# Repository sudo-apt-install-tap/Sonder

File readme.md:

<div align="center">

<h1>
  <b>
    SONDER
  </b> 
</h1>

<h3> <b> An ESP32 SD Card MP3 Player with a PCM5102 DAC, a 0.96" OLED and a Rotary Encoder! </b> </h3>

</div>

## **Overview**

An MP3 player built around an **ESP32** dev board and a **PCM5102** I2S DAC. It plays music from an SD card, shows the current track on a 0.96" OLED, and has 4 buttons (previous, play/pause, next, menu) plus a rotary encoder with a push switch. It lives in a 3D printed case with openings for the aux jack and USB-B port.

### Why?

It started as "wouldn't it be funny if I built my own music player" and then I spent my time fighting KiCad. Further I really wanted to make a project that deals with embedded audio decoding in C/ARDUINO IDE.

### How?
Use the firmware in [FIRMWARE](Firmware). I used ARDUINO IDE with some basic libraries like SPI, SD, vector, Audio & U8g2lib

## CAD
CAD files are available at [CAD](https://cad.onshape.com/documents/66bd644b255fcec0873fcebe/w/d2b2d33a9ff288106fcfa12e/e/8a27dd1411d3c83e2866f539?renderMode=0&uiState=6ae774908fb952af58be5994)

The case is a two part design: a main body that holds the PCB, and a separate front plate with cutouts for the OLED, the buttons and the encoder. The plate outline was drawn in KiCad on the Edge.Cuts layer and exported as a DXF. The PCB mounts to the case with heat set inserts and M2 screws, and the whole thing is 3D printed.

## Images
<div align="center">

<br> Full render<br>

---

<br> Case body

---

<br> Front plate

---

<br> PCB

---

<br> Sch

---

<br> 3D Viewer

---

</div>

## BOM

| Part | What it's for | Qty | Unit | Total | Vendor |
| --- | --- | --- | --- | --- | --- |
| [PCB](https://jlcpcb.com/) | Printed circuit board | 1 | $1.50 | $1.50 | [JLCPCB](https://jlcpcb.com/) |
| [PCM5102 I2S Digital Audio DAC Decoder Module](https://hubtronics.in/pcm5102-i2s-digital-audio-dac-decoder-module) | I2S audio output | 1 | $5.00 | $5.00 | [Hubtronics](https://hubtronics.in/pcm5102-i2s-digital-audio-dac-decoder-module) |
| [Robocraze ESP32 38 Pin](https://www.amazon.in/dp/B078MNG9D5) | MCU | 1 | $6.50 | $6.50 | [Amazon](https://www.amazon.in/dp/B078MNG9D5) |
| [SD Card Reader Module](https://robu.in/product/micro-sd-card-module/) | Reads the SD card over SPI | 1 | $1.00 | $1.00 | [Robu.in](https://robu.in/product/micro-sd-card-module/) |
| [0.96 Inch I2C/IIC 4pin OLED Display](https://robu.in/product/4pin-oled-display-module-blue-color/) | Shows the current track and volume | 1 | $2.00 | $2.00 | [Robu.in](https://robu.in/product/4pin-oled-display-module-blue-color/) |
| [Rotary Encoder with Switch](https://robu.in/product/hongyan-ec11h-7ce20p1zd20-rotary-encoder-with-push-button-switch-vertical-plug-in-5-pin/) | Volume and push | 1 | $1.00 | $1.00 | [Robu.in](https://robu.in/product/hongyan-ec11h-7ce20p1zd20-rotary-encoder-with-push-button-switch-vertical-plug-in-5-pin/) |
| [Tactile push buttons 6x6x8 [Pack of 20]](https://robu.in/product/6x6x8mm-tactile-push-button-switch-pack-of-20/) | Previous, play/pause, next, menu | 1 | $0.50 | $0.50 | [Robu.in](https://robu.in/product/6x6x8mm-tactile-push-button-switch-pack-of-20/) |
| [HIKVISION Extreme 16GB microSDXC Memory Card](https://www.amazon.in/HIKVISION-microSDXC-Compitable-Smartphones-Protection/dp/B0GVJZ56K5) | Stores the music | 1 | $6.50 | $6.50 | [Amazon](https://www.amazon.in/HIKVISION-microSDXC-Compitable-Smartphones-Protection/dp/B0GVJZ56K5) |
| [Case 3D printing](https://hackclub.slack.com/archives/C083P4FJM46/p1793539514844309) | Case | 1 | $3.00 | $3.00 | [Print Legion](https://hackclub.slack.com/archives/C083P4FJM46/p1793539514844309) |
| **Parts subtotal** | — | — | — | **$27.00** | — |
| **Tax & shipping** | — | — | — | **$3.00** | — |
| **Total** | — | — | — | **$30.00** | — |

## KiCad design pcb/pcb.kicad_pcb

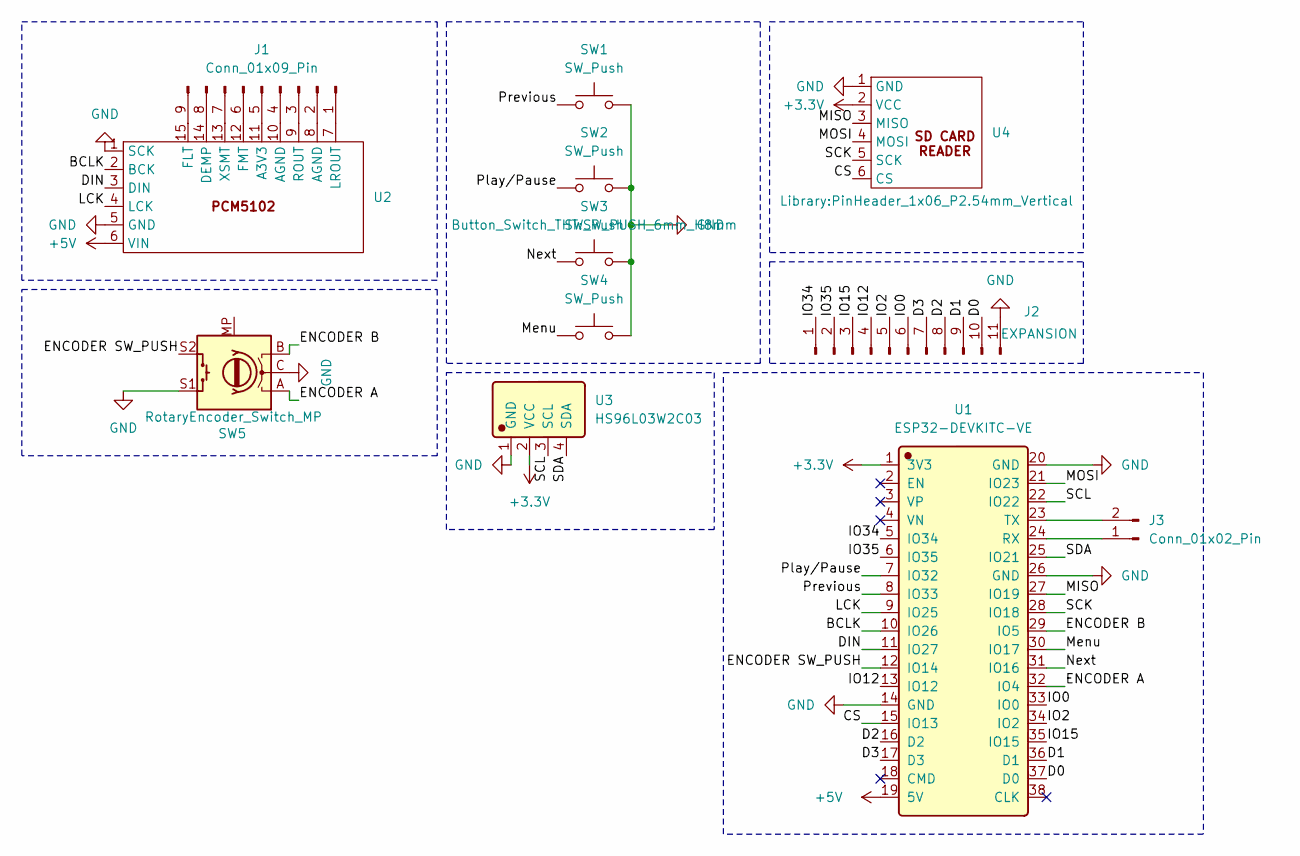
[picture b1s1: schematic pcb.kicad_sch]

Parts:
J1: Conn_01x09_Pin; PinHeader_1x09_P2.54mm_Vertical
J2: EXPANSION; PinHeader_1x11_P2.54mm_Vertical
J3: Conn_01x02_Pin; PinHeader_1x02_P2.54mm_Vertical
SW1, SW2, SW3, SW4: SW_Push; SW_PUSH_6mm_H8mm
SW5: RotaryEncoder_Switch_MP; RotaryEncoder_Alps_EC11E-Switch_Vertical_H20mm_CircularMoun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
U1: ESP32-DEVKITC-VE; Manufacturer Part ESP32-DEVKITC-VE; LCSC C20437001
U2: GY-PCM5102
U3: HS96L03W2C03; Manufacturer Part HS96L03W2C03; LCSC C5248080
U4: PinHeader_1x06_P2.54mm_Vertical

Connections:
+3.3V: U1.1 (3V3), U3.2 (VCC), U4.2 (VCC)
+5V: U1.19 (5V), U2.6 (VIN)
/BCLK: U1.10 (IO26), U2.2 (BCK)
/CS: U1.15 (IO13), U4.6 (CS)
/D0: J2.10, U1.37 (D0)
/D1: J2.9, U1.36 (D1)
/D2: J2.8, U1.16 (D2)
/D3: J2.7, U1.17 (D3)
/DIN: U1.11 (IO27), U2.3 (DIN)
/ENCODER A: SW5.A, U1.32 (IO4)
/ENCODER B: SW5.B, U1.29 (IO5)
/ENCODER SW_PUSH: SW5.S2, U1.12 (IO14)
/IO0: J2.6, U1.33 (IO0)
/IO2: J2.5, U1.34 (IO2)
/IO12: J2.4, U1.13 (IO12)
/IO15: J2.3, U1.35 (IO15)
/IO34: J2.1, U1.5 (IO34)
/IO35: J2.2, U1.6 (IO35)
/LCK: U1.9 (IO25), U2.4 (LCK)
/MISO: U1.27 (IO19), U4.3 (MISO)
/MOSI: U1.21 (IO23), U4.4 (MOSI)
/Menu: SW4.1, U1.30 (IO17)
/Next: SW3.1, U1.31 (IO16)
/Play/Pause: SW2.1, U1.7 (IO32)
/Previous: SW1.1, U1.8 (IO33)
/SCK: U1.28 (IO18), U4.5 (SCK)
/SCL: U1.22 (IO22), U3.3 (SCL)
/SDA: U1.25 (IO21), U3.4 (SDA)
GND: J2.11, SW1.2, SW2.2, SW3.2, SW4.2, SW5.C, SW5.S1, U1.14 (GND), U1.20 (GND), U1.26 (GND), U2.1 (SCK), U2.5 (GND), U3.1 (GND), U4.1 (GND)
unnamed: J1.1, U2.7 (LROUT)
unnamed: J1.2, U2.8 (AGND)
unnamed: J1.3, U2.9 (ROUT)
unnamed: J1.4, U2.10 (AGND)
unnamed: J1.5, U2.11 (A3V3)
unnamed: J1.6, U2.12 (FMT)
unnamed: J1.7, U2.13 (XSMT)
unnamed: J1.8, U2.14 (DEMP)
unnamed: J1.9, U2.15 (FLT)
unnamed: J3.1, U1.24 (RX)
unnamed: J3.2, U1.23 (TX)

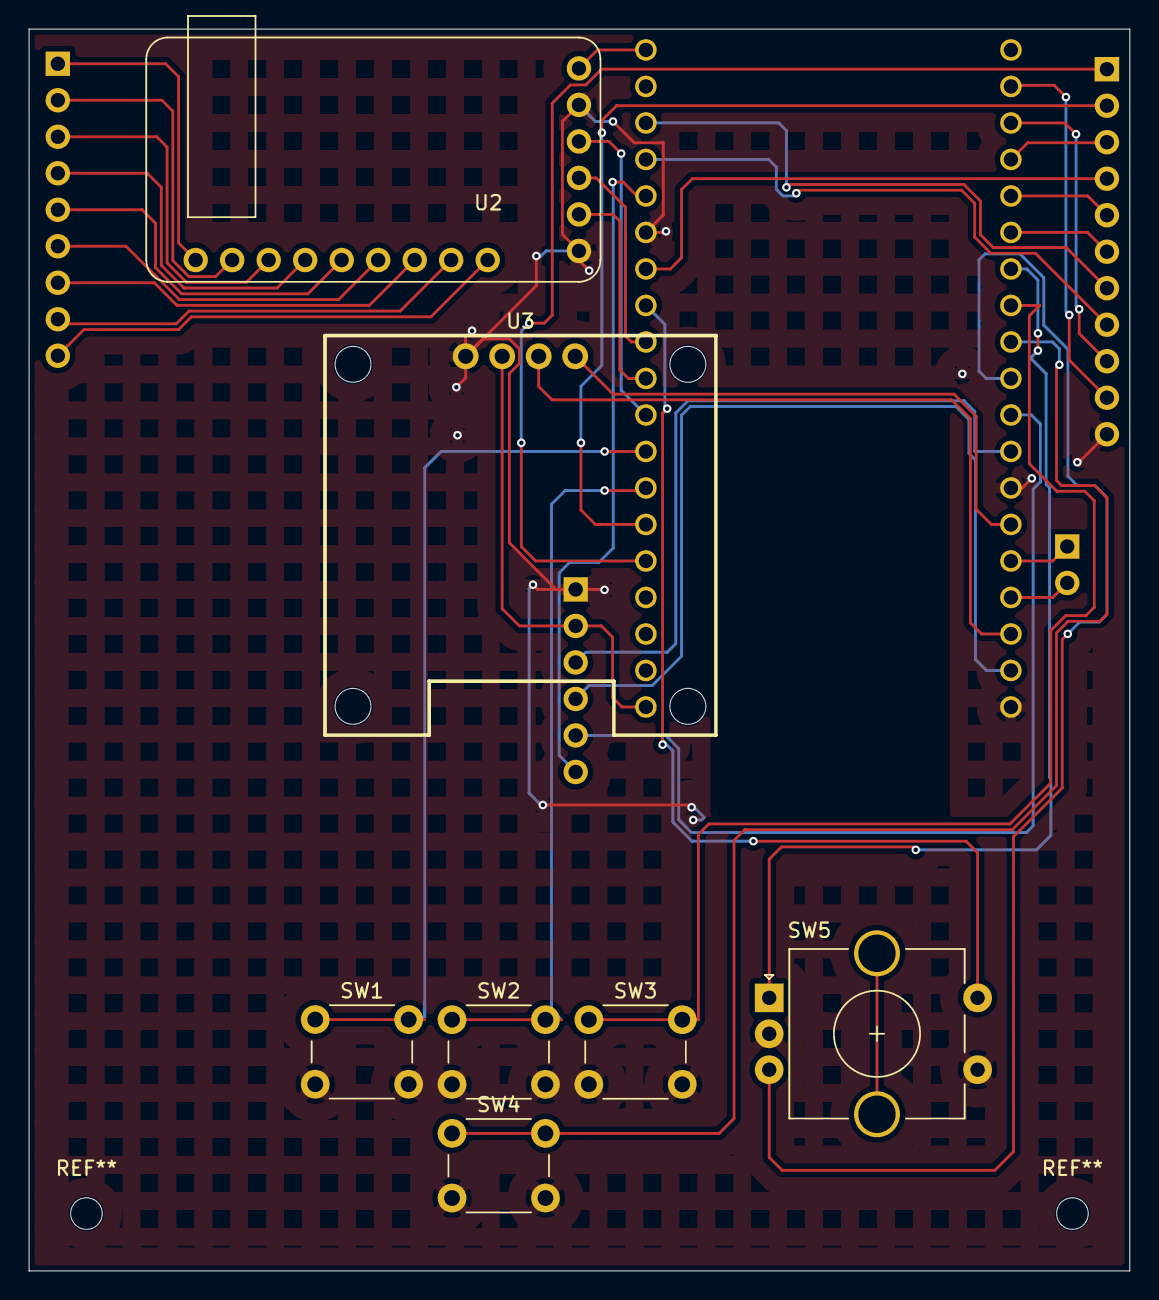
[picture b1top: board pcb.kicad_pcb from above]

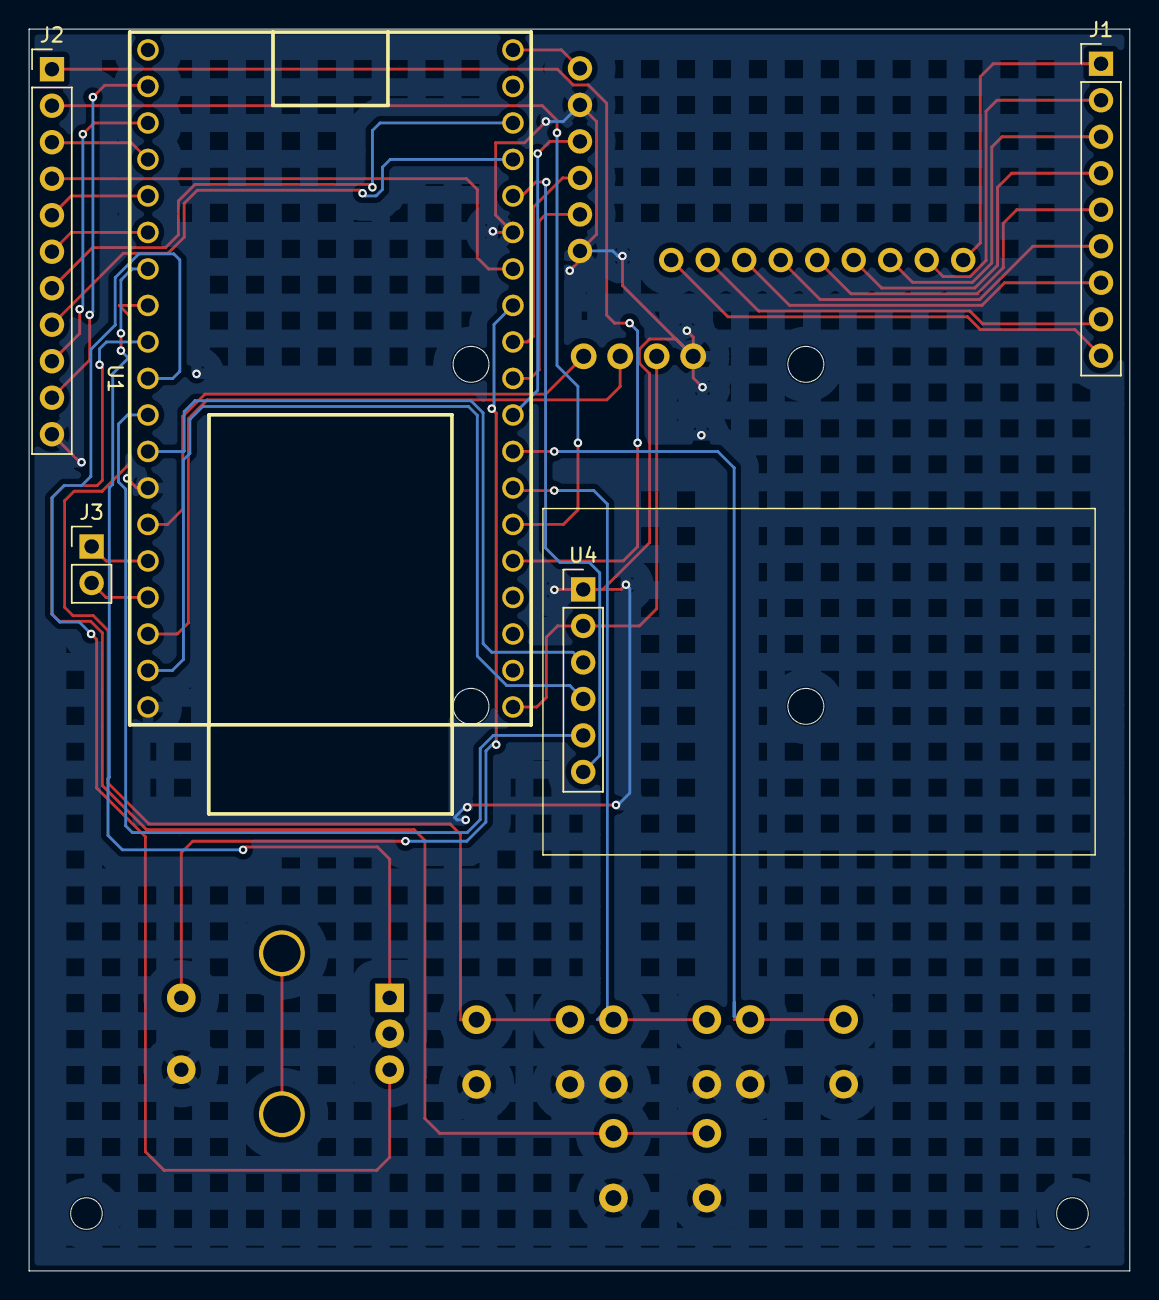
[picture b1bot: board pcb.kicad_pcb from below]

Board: 2 copper layers, 76.6 x 86.4 mm, 12 parts (5 on the bottom side), 40 nets.

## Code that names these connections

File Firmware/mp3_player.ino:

#include <Arduino.h>
#include <SPI.h>
#include <SD.h>
#include <vector>
#include <algorithm>
#include <Audio.h>
#include <U8g2lib.h>

// I2S -> PCM5102
constexpr int PIN_I2S_BCK  = 26;  // BCLK
constexpr int PIN_I2S_LRC  = 25;  // LCK
constexpr int PIN_I2S_DOUT = 27;  // DIN

// SD card (SPI)
constexpr int PIN_SD_SCK  = 18;
constexpr int PIN_SD_MISO = 19;
constexpr int PIN_SD_MOSI = 23;
constexpr int PIN_SD_CS   = 13;

// OLED (I2C)
constexpr int PIN_OLED_SDA = 21;
constexpr int PIN_OLED_SCL = 22;

// Buttons (SW1..SW4, each wired to GND)
constexpr int PIN_BTN_PREV = 33;  // SW1 "Previous"
constexpr int PIN_BTN_PLAY = 32;  // SW2 "Play/Pause"
constexpr int PIN_BTN_NEXT = 16;  // SW3 "Next"
constexpr int PIN_BTN_MODE = 17;  // SW4 "Menu"

// Rotary encoder
constexpr int PIN_ENC_A  = 4;
constexpr int PIN_ENC_B  = 5;
constexpr int PIN_ENC_SW = 14;
// =========================================================================

constexpr int VOLUME_MAX = 21;  // ESP32-audioI2S volume range is 0..21

SPIClass sdSPI(VSPI);
Audio audio;

U8G2_SSD1306_128X64_NONAME_F_HW_I2C display(U8G2_R0, U8X8_PIN_NONE,
                                            PIN_OLED_SCL, PIN_OLED_SDA);

std::vector<String> tracks;
int  current = 0;
int  volume = 8;
bool paused = false;
bool stopped = false;
bool shuffle = false;
bool muted = false;
bool dirty = true;
uint32_t trackStartMs = 0;
uint32_t lastDrawMs = 0;
int failCount = 0;

// ---------------------------- buttons ----------------------------------
struct Button {
  uint8_t pin;
  bool last;
  uint32_t t;
};

Button btnPrev{PIN_BTN_PREV, HIGH, 0};
Button btnPlay{PIN_BTN_PLAY, HIGH, 0};
Button btnNext{PIN_BTN_NEXT, HIGH, 0};
Button btnMode{PIN_BTN_MODE, HIGH, 0};
Button btnEnc {PIN_ENC_SW,   HIGH, 0};

bool pressed(Button &b) {
  bool now = digitalRead(b.pin);
  if (now != b.last && millis() - b.t > 30) {
    b.t = millis();
    b.last = now;
    if (now == LOW) return true;
  }
  return false;
}


int8_t readEncoder() {
  static uint8_t prev = 0;
  static int8_t acc = 0;
  static const int8_t table[16] = {0, -1, 1, 0, 1, 0, 0, -1,
                                   -1, 0, 0, 1, 0, 1, -1, 0};
  uint8_t cur = (digitalRead(PIN_ENC_A) << 1) | digitalRead(PIN_ENC_B);
  prev = ((prev << 2) | cur) & 0x0F;
  acc += table[prev];
  if (acc >= 4)  { acc = 0; return 1; }
  if (acc <= -4) { acc = 0; return -1; }
  return 0;
}

// ---------------------------- display ----------------------------------
void draw() {
  display.clearBuffer();
  display.setFont(u8g2_font_6x10_tr);
  char line[32];

  if (tracks.empty()) {
    display.drawStr(0, 12, "No tracks on SD");
  } else {
    snprintf(line, sizeof(line), "%d/%d %s%s", current + 1, (int)tracks.size(),
             shuffle ? "SHF " : "", muted ? "MUTE" : "");
    display.drawStr(0, 10, line);
    display.drawStr(0, 26, tracks[current].substring(0, 21).c_str());
    display.drawStr(0, 42, stopped ? "STOPPED" : (paused ? "PAUSED" : "PLAYING"));
  }

  int level = muted ? 0 : volume;
  display.drawFrame(0, 54, 100, 8);
  display.drawBox(0, 54, (level * 100) / VOLUME_MAX, 8);
  display.sendBuffer();

  dirty = false;
  lastDrawMs = millis();
}

void showMessage(const char *msg) {
  display.clearBuffer();
  display.setFont(u8g2_font_6x10_tr);
  display.drawStr(0, 12, msg);
  display.sendBuffer();
}

// ---------------------------- SD / tracks ------------------------------
void scanTracks() {
  File root = SD.open("/");
  if (!root) return;
  while (true) {
    File f = root.openNextFile();
    if (!f) break;
    String name = f.name();
    bool isDir = f.isDirectory();
    f.close();

    int slash = name.lastIndexOf('/');
    if (slash >= 0) name = name.substring(slash + 1);
    if (isDir || name.startsWith(".")) continue;  // skips hidden/._ files

    String lower = name;
    lower.toLowerCase();
    if (lower.endsWith(".mp3") || lower.endsWith(".wav") || lower.endsWith(".flac")) {
      tracks.push_back(name);
    }
  }
  root.close();
  std::sort(tracks.begin(), tracks.end(),
            [](const String &a, const String &b) { return a.compareTo(b) < 0; });
}

// ---------------------------- playback ---------------------------------
void playTrack(int index) {
  if (tracks.empty()) return;
  int n = tracks.size();
  current = ((index % n) + n) % n;
  String path = "/" + tracks[current];


  if (millis() - trackStartMs < 1000) failCount++; else failCount = 0;
  if (failCount >= n) {
    stopped = true;
    dirty = true;
    return;
  }

  audio.connecttoFS(SD, path.c_str());
  trackStartMs = millis();
  paused = false;
  stopped = false;
  dirty = true;
}

void nextTrack() {
  int n = tracks.size();
  if (n == 0) return;
  if (shuffle && n > 1) {
    int r;
    do { r = esp_random() % n; } while (r == current);
    playTrack(r);
  } else {
    playTrack(current + 1);
  }
}

void prevTrack() { playTrack(current - 1); }

void togglePause() {
  if (stopped) { playTrack(current); return; }
  audio.pauseResume();
  paused = !paused;
  dirty = true;
}

void applyVolume() {
  audio.setVolume(muted ? 0 : volume);
  dirty = true;
}

// ----------------------------- setup / loop ----------------------------
void setup() {
  Serial.begin(115200);

  pinMode(PIN_BTN_PREV, INPUT_PULLUP);
  pinMode(PIN_BTN_PLAY, INPUT_PULLUP);
  pinMode(PIN_BTN_NEXT, INPUT_PULLUP);
  pinMode(PIN_BTN_MODE, INPUT_PULLUP);
  pinMode(PIN_ENC_A, INPUT_PULLUP);
  pinMode(PIN_ENC_B, INPUT_PULLUP);
  pinMode(PIN_ENC_SW, INPUT_PULLUP);

  display.begin();
  showMessage("Booting...");

  sdSPI.begin(PIN_SD_SCK, PIN_SD_MISO, PIN_SD_MOSI, PIN_SD_CS);
  if (!SD.begin(PIN_SD_CS, sdSPI)) {
    showMessage("SD init failed");
    while (true) delay(1000);
  }
  scanTracks();

  audio.setPinout(PIN_I2S_BCK, PIN_I2S_LRC, PIN_I2S_DOUT);
  audio.setVolume(volume);

  if (!tracks.empty()) playTrack(0);
  dirty = true;
}

void loop() {
  audio.loop();

  if (pressed(btnPlay)) togglePause();
  if (pressed(btnNext)) nextTrack();
  if (pressed(btnPrev)) prevTrack();
  if (pressed(btnMode)) { shuffle = !shuffle; dirty = true; }
  if (pressed(btnEnc))  { muted = !muted; applyVolume(); }

  int8_t step = readEncoder();
  if (step != 0) {
    volume = constrain(volume + step, 0, VOLUME_MAX);
    muted = false;
    applyVolume();
  }

  if (!tracks.empty() && !paused && !stopped && !audio.isRunning() &&
      millis() - trackStartMs > 300) {
    nextTrack();
  }

  if (dirty && millis() - lastDrawMs > 100) draw();
}
